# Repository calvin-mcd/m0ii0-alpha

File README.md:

# m0ii0-alpha

alpha stagger pcb for the 40% kaWaii m0ii0 by [yohewi](https://github.com/yohewi).
 
## Layout

[Link](https://www.keyboard-layout-editor.com/#/gists/c427c1bf705222f226298ba031b6538b)

## Todo

- [x] order & test pcb

## Disclaimer

This PCB has been fully tested and confirmed to work. The members of the PCB development team are however not liable if you end up with a non-functional pcb. Order at your own risk. Support will not be provided but pull requests will be reviewed and possibly accepted.

## License

This project is released under the GPL v3 License. Please refer to the LICENCE file.

## Credits
	
As always big thanks to the many people who helped me and inspired this board!

Any questions, contact Calvin0563 on Discord.

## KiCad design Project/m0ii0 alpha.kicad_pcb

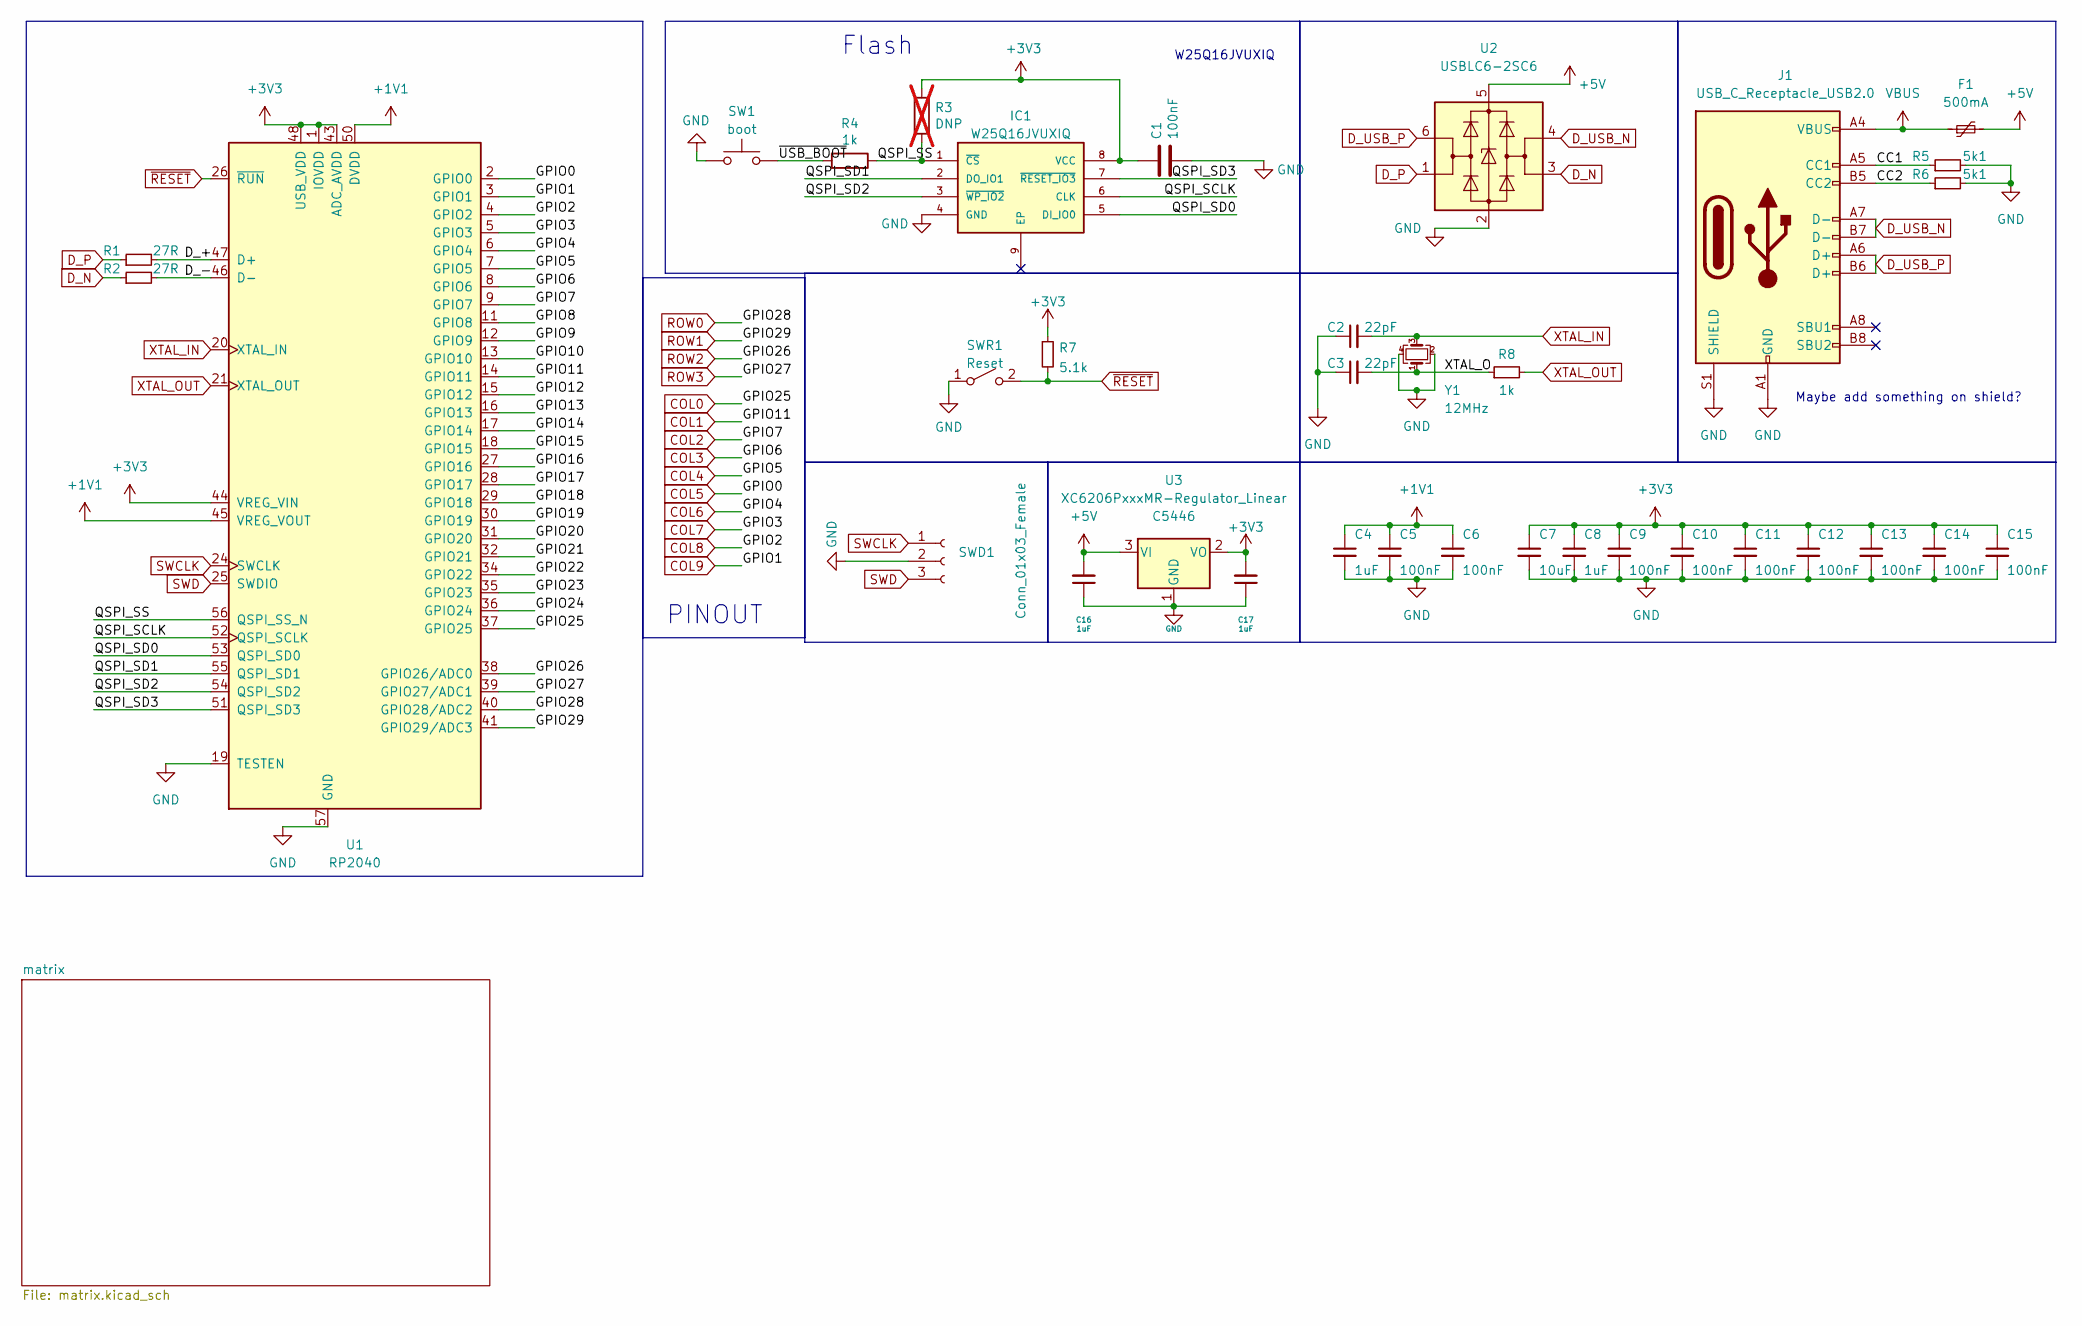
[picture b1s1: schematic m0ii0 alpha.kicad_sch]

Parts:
C1, C5, C6, C9, C10, C11, C12, C13, C14, C15: 100nF; C_0402_1005Metric; LCSC C1525
C2, C3: 22pF; C_0402_1005Metric; LCSC C1555
C4, C8, C16, C17: 1uF; C_0402_1005Metric; LCSC C52923
C7: 10uF; C_0402_1005Metric; LCSC C15525
F1: 500mA; Fuse_1206_3216Metric; LCSC C70076
IC1: W25Q16JVUXIQ; SON50P300X200X60-9N; MANUFACTURER_PART_NUMBER W25Q16JVUXIQ; LCSC Part C2843335
J1: USB_C_Receptacle_USB2.0; USB_C_Receptacle_HRO_TYPE-C-31-M-12; LCSC C165948
R1, R2: 27R; R_0603_1608Metric; LCSC C25190
R3: DNP; C_0402_1005Metric; LCSC C25905; not fitted
R4: 1k; R_0402_1005Metric; LCSC Part C25543
R5, R6: 5k1; R_0402_1005Metric; LCSC C25905
R7: 5.1k; R_0402_1005Metric
R8: 1k; R_0402_1005Metric; LCSC C11702
SW1: boot; SW_Push_SPST_NO_Alps_SKRK; LCSC Part C115351
SWD1: Conn_01x03_Female; PinHeader_1x03_P2.54mm_Vertical
SWR1: Reset; SW_Push_SPST_NO_Alps_SKRK
U1: RP2040; RP2040-QFN-56; LCSC C2040
U2: USBLC6-2SC6; SOT-23-6; LCSC C2827654
U3: XC6206PxxxMR-Regulator_Linear; SOT-23; LCSC C5446
Y1: 12MHz; Crystal_SMD_3225-4Pin_3.2x2.5mm; LCSC C9002

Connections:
+1V1: C4.1, C5.1, C6.1, U1.23 (DVDD), U1.45 (VREG_VOUT), U1.50 (DVDD)
+3V3: C1.1, C7.1, C8.1, C9.1, C10.1, C11.1, C12.1, C13.1, C14.1, C15.1, C17.2, IC1.8 (VCC), R3.1, R7.1, U1.1 (IOVDD), U1.10 (IOVDD), U1.22 (IOVDD), U1.33 (IOVDD), U1.42 (IOVDD), U1.43 (ADC_AVDD), U1.44 (VREG_VIN), U1.48 (USB_VDD), U1.49 (IOVDD), U3.2 (VO)
+5V: C16.2, F1.2, U2.5 (VBUS), U3.3 (VI)
/CC1: J1.A5 (CC1), R5.1
/CC2: J1.B5 (CC2), R6.1
/D_+: R1.2, U1.47 (D+)
/D_-: R2.2, U1.46 (D-)
/GPIO8: U1.11 (GPIO8)
/GPIO9: U1.12 (GPIO9)
/GPIO10: U1.13 (GPIO10)
/GPIO12: U1.15 (GPIO12)
/GPIO13: U1.16 (GPIO13)
/GPIO14: U1.17 (GPIO14)
/GPIO15: U1.18 (GPIO15)
/GPIO16: U1.27 (GPIO16)
/GPIO17: U1.28 (GPIO17)
/GPIO18: U1.29 (GPIO18)
/GPIO19: U1.30 (GPIO19)
/GPIO20: U1.31 (GPIO20)
/GPIO21: U1.32 (GPIO21)
/GPIO22: U1.34 (GPIO22)
/GPIO23: U1.35 (GPIO23)
/GPIO24: U1.36 (GPIO24)
/QSPI_SCLK: IC1.6 (CLK), U1.52 (QSPI_SCLK)
/QSPI_SD0: IC1.5 (DI_IO0), U1.53 (QSPI_SD0)
/QSPI_SD1: IC1.2 (DO_IO1), U1.55 (QSPI_SD1)
/QSPI_SD2: IC1.3 (~WP_IO2), U1.54 (QSPI_SD2)
/QSPI_SD3: IC1.7 (~RESET_IO3), U1.51 (QSPI_SD3)
/QSPI_SS: IC1.1 (~CS), R3.2, R4.1, U1.56 (QSPI_SS_N)
/XTAL_O: C3.2, R8.1, Y1.1
/~USB_BOOT: R4.2, SW1.2
COL0: U1.37 (GPIO25); also elsewhere on the board
COL1: U1.14 (GPIO11); also elsewhere on the board
COL2: U1.9 (GPIO7); also elsewhere on the board
COL3: U1.8 (GPIO6); also elsewhere on the board
COL4: U1.7 (GPIO5); also elsewhere on the board
COL5: U1.2 (GPIO0); also elsewhere on the board
COL6: U1.6 (GPIO4); also elsewhere on the board
COL7: U1.5 (GPIO3); also elsewhere on the board
COL8: U1.4 (GPIO2); also elsewhere on the board
COL9: U1.3 (GPIO1); also elsewhere on the board
D_N: R2.1, U2.3 (I/O2)
D_P: R1.1, U2.1 (I/O1)
D_USB_N: J1.A7 (D-), J1.B7 (D-), U2.4 (I/O2)
D_USB_P: J1.A6 (D+), J1.B6 (D+), U2.6 (I/O1)
GND: C1.2, C2.1, C3.1, C4.2, C5.2, C6.2, C7.2, C8.2, C9.2, C10.2, C11.2, C12.2, C13.2, C14.2, C15.2, C16.1, C17.1, IC1.4 (GND), J1.A1 (GND), J1.A12 (GND), J1.B1 (GND), J1.B12 (GND), J1.S1 (SHIELD), R5.2, R6.2, SW1.1, SWD1.2, SWR1.1 (A), U1.19 (TESTEN), U1.57 (GND), U2.2 (GND), U3.1 (GND), Y1.2, Y1.4
ROW0: U1.40 (GPIO28/ADC2); also elsewhere on the board
ROW1: U1.41 (GPIO29/ADC3); also elsewhere on the board
ROW2: U1.38 (GPIO26/ADC0); also elsewhere on the board
ROW3: U1.39 (GPIO27/ADC1); also elsewhere on the board
SWCLK: SWD1.1, U1.24 (SWCLK)
SWD: SWD1.3, U1.25 (SWDIO)
VBUS: F1.1, J1.A4 (VBUS), J1.A9 (VBUS), J1.B4 (VBUS), J1.B9 (VBUS)
XTAL_IN: C2.2, U1.20 (XTAL_IN), Y1.3
XTAL_OUT: R8.2, U1.21 (XTAL_OUT)
~RESET: R7.2, SWR1.2 (B), U1.26 (~RUN)

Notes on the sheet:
Flash
Maybe add something on shield?
PINOUT
W25Q16JVUXIQ

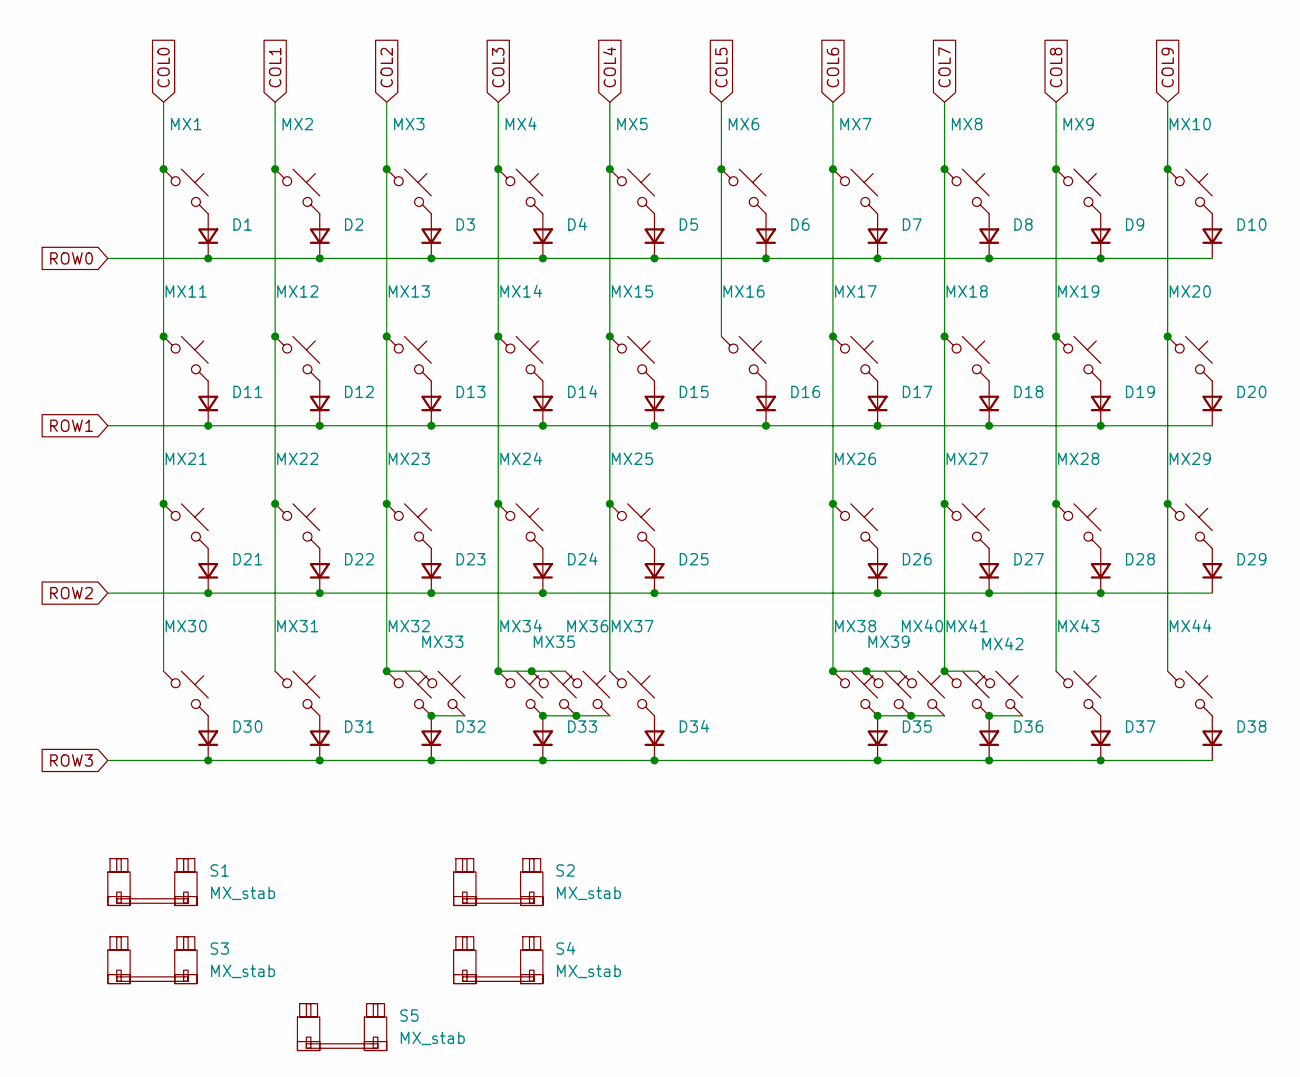
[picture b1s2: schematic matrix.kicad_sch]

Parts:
D1, D2, D3, D4, D5, D6, D7, D8, D9, D10, D11, D12, D13, D14, D15, D16, D17, D18, D19, D20, D21, D22, D23, D24, D25, D26, D27, D28, D29, D30, D31, D32, D33, D34, D35, D36, D37, D38: D_Small; D_SOD-123F
MX1, MX2, MX3, MX4, MX5, MX6, MX7, MX8, MX9, MX10, MX11, MX12, MX13, MX14, MX15, MX16, MX17, MX18, MX19, MX20, MX22, MX23, MX24, MX25, MX26, MX27, MX28, MX30, MX31, MX32, MX34, MX35, MX37, MX38, MX39, MX41, MX43, MX44: MX_SW_solder; SW_MX_1u
MX21, MX29: MX_SW_solder; SW_MX_1.5u
MX33, MX42: MX_SW_solder; SW_MX_1.25u
MX36, MX40: MX_SW_solder; SW_MX_1.75u
S1, S2: MX_stab; STAB_MX_P_2u
S3, S4: MX_stab; STAB_MX_P_3u
S5: MX_stab; STAB_MX_P_6u

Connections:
COL0: MX1.1, MX11.1, MX21.1, MX30.1; also elsewhere on the board
COL1: MX2.1, MX12.1, MX22.1, MX31.1; also elsewhere on the board
COL2: MX3.1, MX13.1, MX23.1, MX32.1, MX33.1; also elsewhere on the board
COL3: MX4.1, MX14.1, MX24.1, MX34.1, MX35.1, MX36.1; also elsewhere on the board
COL4: MX5.1, MX15.1, MX25.1, MX37.1; also elsewhere on the board
COL5: MX6.1, MX16.1; also elsewhere on the board
COL6: MX7.1, MX17.1, MX26.1, MX38.1, MX39.1, MX40.1; also elsewhere on the board
COL7: MX8.1, MX18.1, MX27.1, MX41.1, MX42.1; also elsewhere on the board
COL8: MX9.1, MX19.1, MX28.1, MX43.1; also elsewhere on the board
COL9: MX10.1, MX20.1, MX29.1, MX44.1; also elsewhere on the board
unnamed: D1.2 (A), MX1.2
unnamed: D2.2 (A), MX2.2
unnamed: D3.2 (A), MX3.2
unnamed: D4.2 (A), MX4.2
unnamed: D5.2 (A), MX5.2
unnamed: D6.2 (A), MX6.2
unnamed: D7.2 (A), MX7.2
unnamed: D8.2 (A), MX8.2
unnamed: D9.2 (A), MX9.2
unnamed: D10.2 (A), MX10.2
unnamed: D11.2 (A), MX11.2
unnamed: D12.2 (A), MX12.2
unnamed: D13.2 (A), MX13.2
unnamed: D14.2 (A), MX14.2
unnamed: D15.2 (A), MX15.2
unnamed: D16.2 (A), MX16.2
unnamed: D17.2 (A), MX17.2
unnamed: D18.2 (A), MX18.2
unnamed: D19.2 (A), MX19.2
unnamed: D20.2 (A), MX20.2
unnamed: D21.2 (A), MX21.2
unnamed: D22.2 (A), MX22.2
unnamed: D23.2 (A), MX23.2
unnamed: D24.2 (A), MX24.2
unnamed: D25.2 (A), MX25.2
unnamed: D26.2 (A), MX26.2
unnamed: D27.2 (A), MX27.2
unnamed: D28.2 (A), MX28.2
unnamed: D29.2 (A), MX29.2
unnamed: D30.2 (A), MX30.2
unnamed: D31.2 (A), MX31.2
unnamed: D32.2 (A), MX32.2, MX33.2
unnamed: D33.2 (A), MX34.2, MX35.2, MX36.2
unnamed: D34.2 (A), MX37.2
unnamed: D35.2 (A), MX38.2, MX39.2, MX40.2
unnamed: D36.2 (A), MX41.2, MX42.2
unnamed: D37.2 (A), MX43.2
unnamed: D38.2 (A), MX44.2
ROW0: D1.1 (K), D2.1 (K), D3.1 (K), D4.1 (K), D5.1 (K), D6.1 (K), D7.1 (K), D8.1 (K), D9.1 (K), D10.1 (K); also elsewhere on the board
ROW1: D11.1 (K), D12.1 (K), D13.1 (K), D14.1 (K), D15.1 (K), D16.1 (K), D17.1 (K), D18.1 (K), D19.1 (K), D20.1 (K); also elsewhere on the board
ROW2: D21.1 (K), D22.1 (K), D23.1 (K), D24.1 (K), D25.1 (K), D26.1 (K), D27.1 (K), D28.1 (K), D29.1 (K); also elsewhere on the board
ROW3: D30.1 (K), D31.1 (K), D32.1 (K), D33.1 (K), D34.1 (K), D35.1 (K), D36.1 (K), D37.1 (K), D38.1 (K); also elsewhere on the board

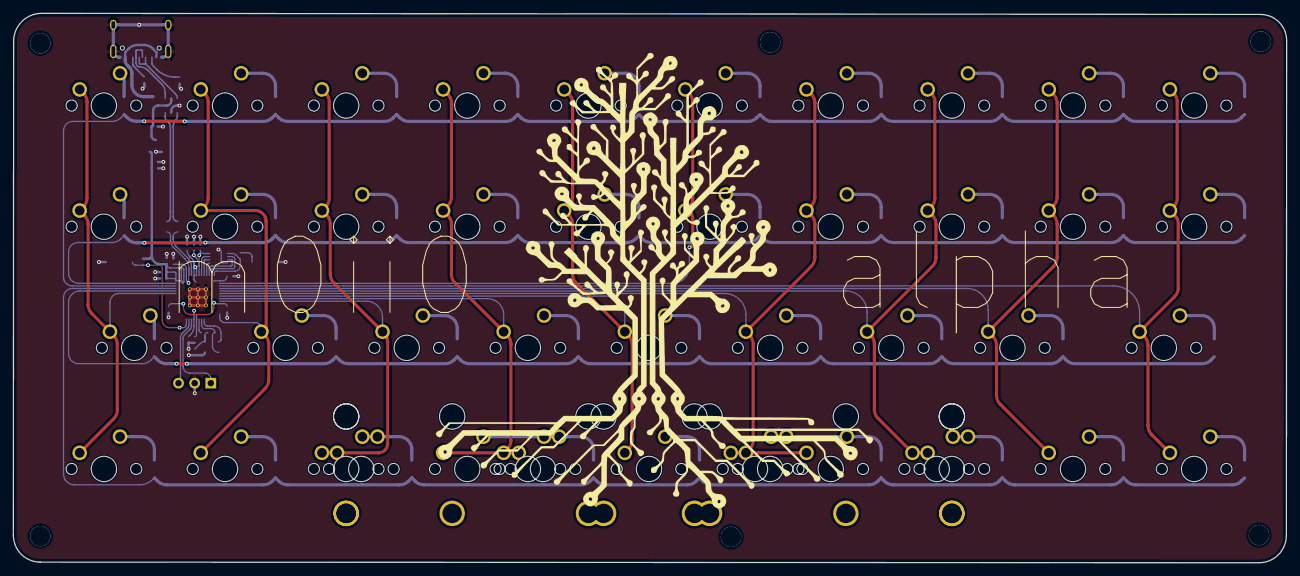
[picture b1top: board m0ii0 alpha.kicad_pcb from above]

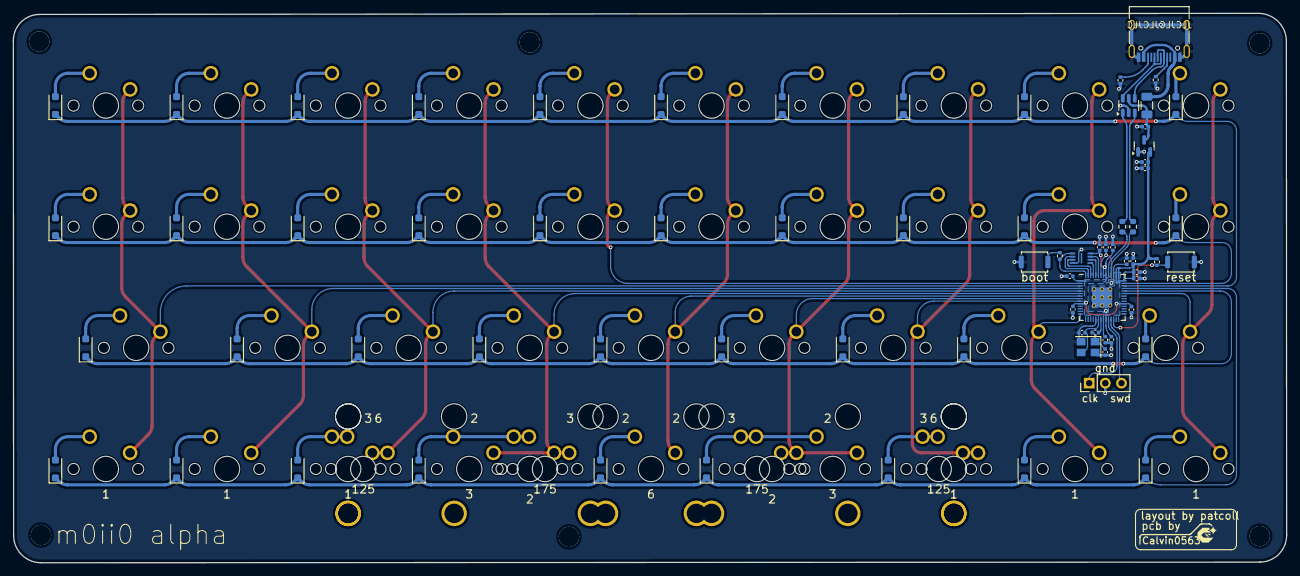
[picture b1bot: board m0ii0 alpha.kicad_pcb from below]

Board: 2 copper layers, 200.2 x 86.4 mm, 121 parts (72 on the bottom side), 78 nets.

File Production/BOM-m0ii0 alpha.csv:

Comment,Designator,Footprint,LCSC
boot,SW1,SW_Push_SPST_NO_Alps_SKRK,C561519
1k,R8,R_0402_1005Metric,C11702
100nF,"C1,C10,C11,C12,C13,C14,C15,C5,C6,C9",C_0402_1005Metric,C1525
10uF,C7,C_0402_1005Metric,C15525
22pF,"C2,C3",C_0402_1005Metric,C1555
USB_C_Receptacle_USB2.0,J1,USB_C_Receptacle_HRO_TYPE-C-31-M-12,C165948
RP2040,U1,RP2040-QFN-56,C2040
27R,"R1,R2",R_0603_1608Metric,C25190
1k,R4,R_0402_1005Metric,C25543
5k1,"R5,R6,R7",R_0402_1005Metric,C25905
USBLC6-2SC6,U2,SOT-23-6,C2827654
W25Q16JVUXIQ,IC1,SON50P300X200X60-9N,C2843335
1uF,"C16,C17,C4,C8",C_0402_1005Metric,C52923
XC6206PxxxMR-Regulator_Linear,U3,SOT-23,C5446
Reset,SWR1,SW_Push_SPST_NO_Alps_SKRK,C561519
500mA,F1,Fuse_1206_3216Metric,C70076
D_Small,"D1,D10,D11,D12,D13,D14,D15,D16,D17,D18,D19,D2,D20,D21,D22,D23,D24,D25,D26,D27,D28,D29,D3,D30,D31,D32,D33,D34,D35,D36,D37,D38,D4,D5,D6,D7,D8,D9",D_SOD-123F,C81598
12MHz,Y1,Crystal_SMD_3225-4Pin_3.2x2.5mm,C9002

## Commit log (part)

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2024-09-22 added silkscreen
2024-09-30 firmware & readmen
2024-12-22 backup
